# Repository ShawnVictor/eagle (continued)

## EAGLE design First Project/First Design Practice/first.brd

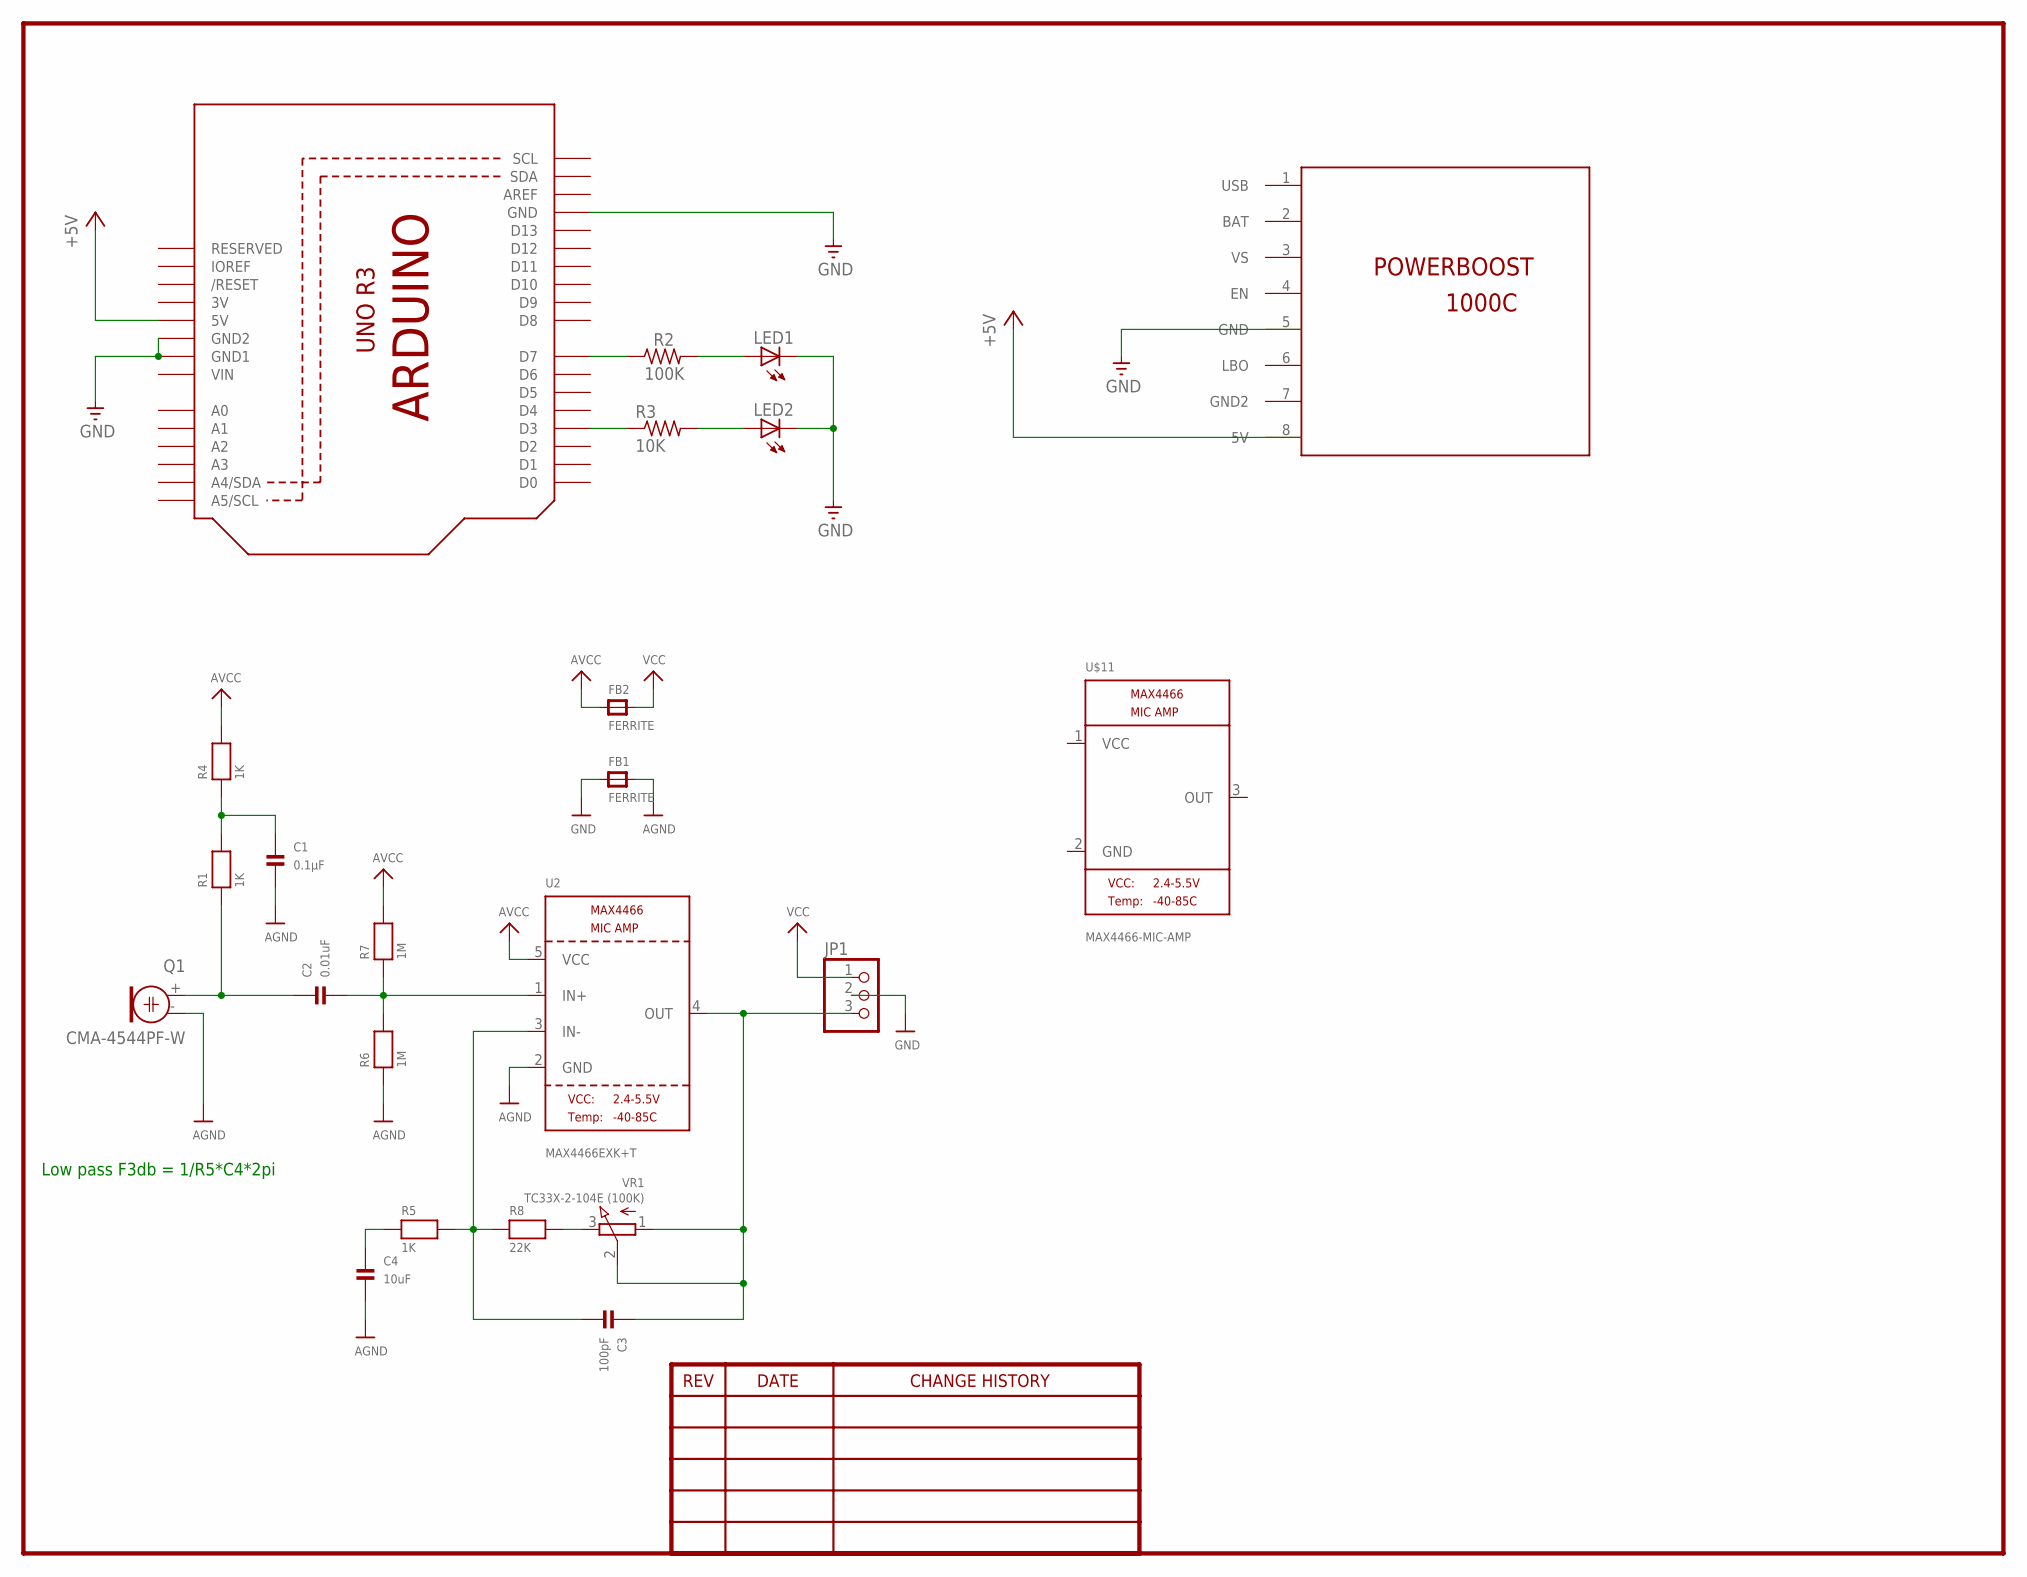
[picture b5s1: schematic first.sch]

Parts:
C1: 0.1µF; 0805
C2: 0.01uF; 0805
C3: 100pF; 0805
C4: 10uF; 0805
FB1, FB2: FERRITE; 0805
JP1: HEADER-1X376MIL; 1X03_ROUND_76
LED1, LED2: LED5MM
Q1: CMA-4544PF-W; ELECTRET_9.7
R1, R4, R5: 1K; 0805
R2: 100K; 0309/10
R3: 10K; 0309/10
R6, R7: 1M; 0805
R8: 22K; 0805
U1: ARDUINOR3-BPLACE
U2: MAX4466EXK+T; SC70-5
U$1: ADAFRUIT-POWERBOOST-1000C
U$11: MAX4466-MIC-AMP; MAX4466
VR1: TC33X-2-104E (100K); TRIMPOT_BOURNS_TC33X-2

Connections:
3V: U1.3V
+5V: U1.5V, U$1.8 (5V)
AGND: C1.2, C4.2, FB1.2, Q1.- (1), R6.1, U2.2 (GND)
AVCC: FB2.1, R4.2, R7.2, U2.5 (VCC)
GND: FB1.1, JP1.2, LED1.K (C), LED2.K (C), U1.GND, U1.GND1, U1.GND2, U$1.5 (GND)
unnamed: R2.1, U1.D7
unnamed: R3.1, U1.D3
unnamed: LED1.A, R2.2
unnamed: C2.1, Q1.+ (2), R1.1
unnamed: LED2.A, R3.2
unnamed: C1.1, R1.2, R4.1
unnamed: C2.2, R6.2, R7.1, U2.1 (IN+)
unnamed: C3.1, JP1.3, U2.4 (OUT), VR1.1 (A), VR1.2 (S)
unnamed: C3.2, R5.2, R8.1, U2.3 (IN-)
unnamed: C4.1, R5.1
unnamed: R8.2, VR1.3 (E)
VCC: FB2.2, JP1.1
VIN: U1.VIN

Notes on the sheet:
Low pass F3db = 1/R5*C4*2pi

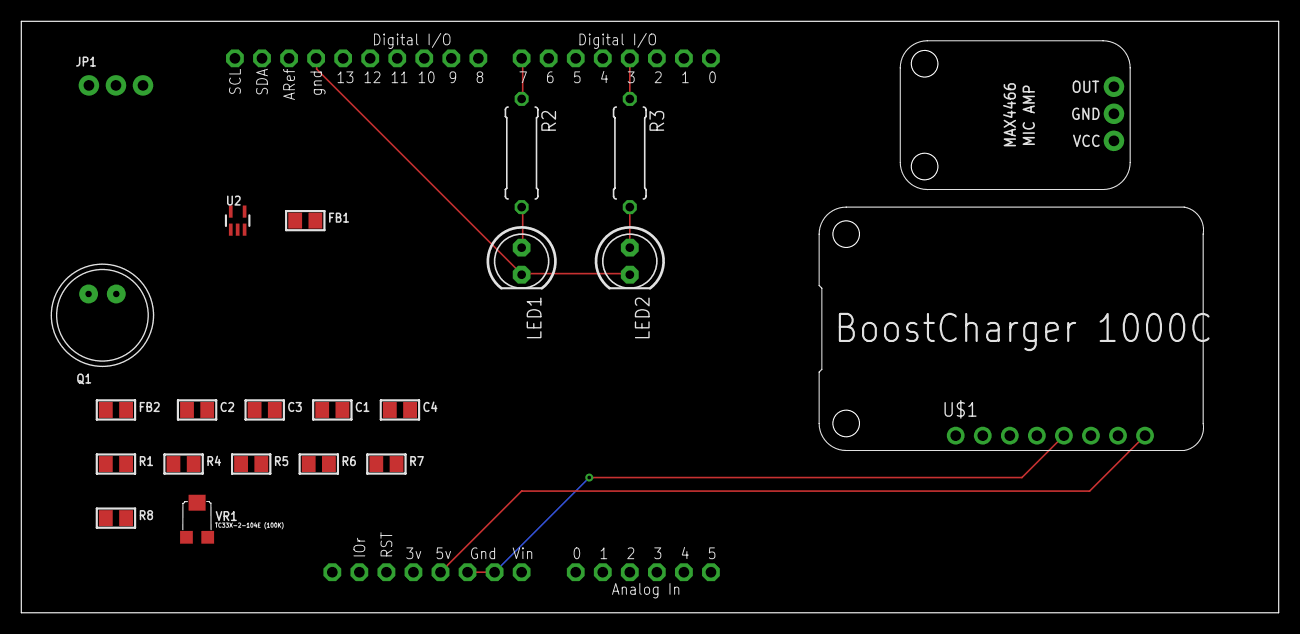
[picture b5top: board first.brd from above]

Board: 2 copper layers, 118.1 x 55.5 mm, 23 parts (0 on the bottom side), 16 nets.

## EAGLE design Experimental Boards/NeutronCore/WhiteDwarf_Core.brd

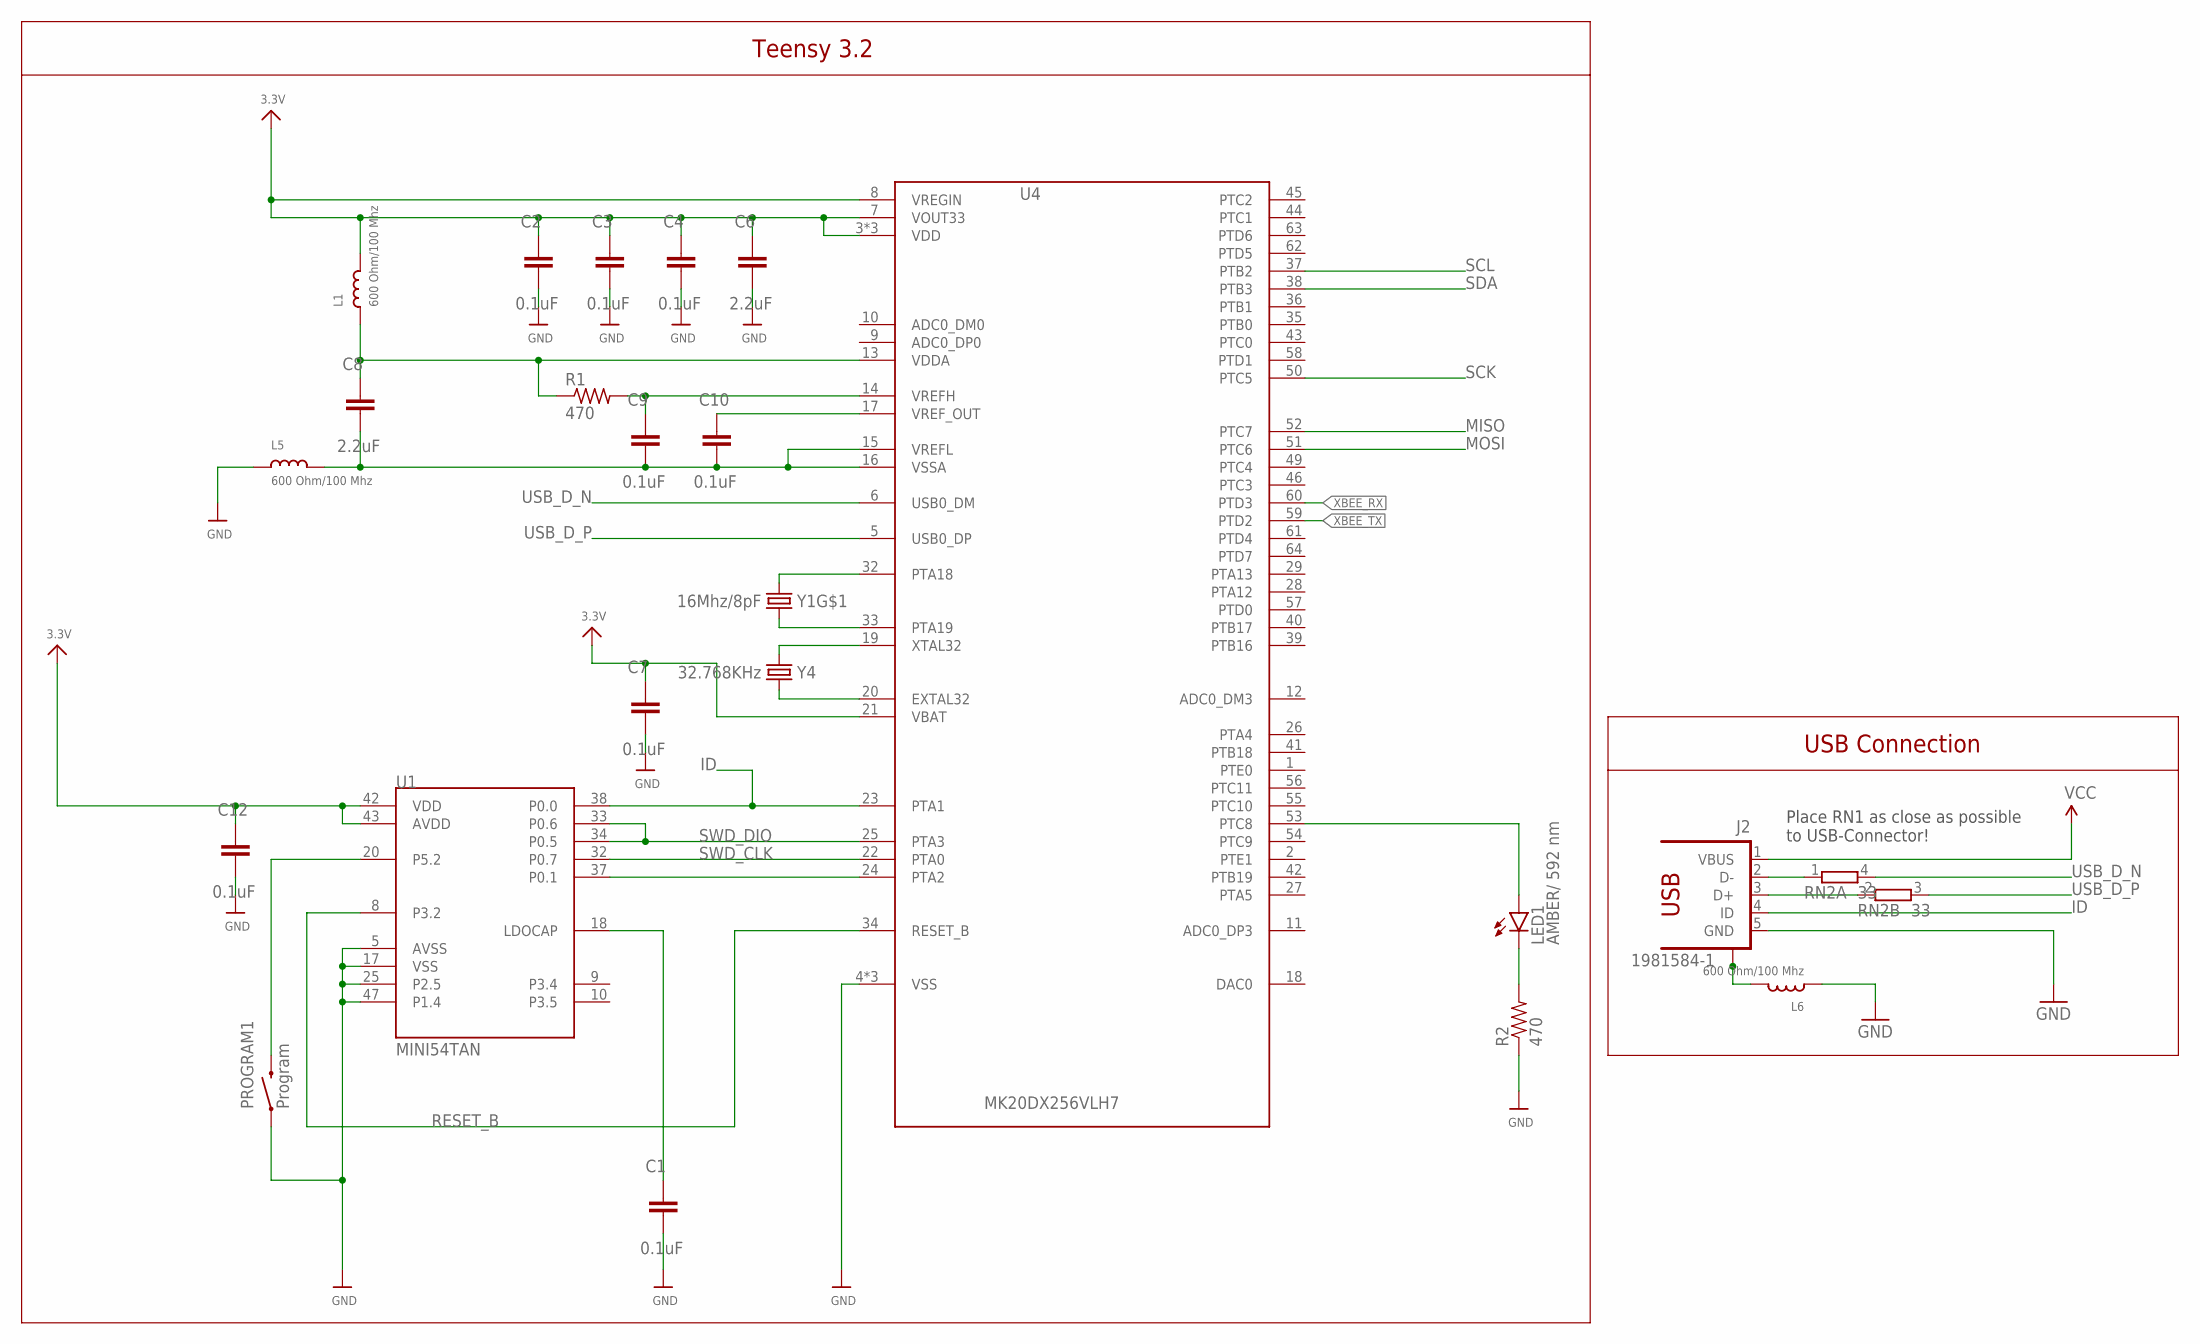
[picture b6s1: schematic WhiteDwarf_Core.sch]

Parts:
C1, C2, C3, C4, C7, C9, C10, C12: 0.1uF; CAP_0402
C6, C8: 2.2uF; CAP_0402
J2: 1981584-1; MPN ZX62-AB-5PA(11)
L1, L5, L6: 600 Ohm/100 Mhz; 0805
LED1: AMBER/ 592 nm; LED-0603
PROGRAM1: Program; TACTILE-SWITCH-1101NE; MPN RS-282G05A3-SM RT
R1: 470; RES_0402
R2: 470; 0603-RES
RN2: 33; EXB34V; MPN EXB-34V330JV
U1: MINI54TAN
U4: MK20DX256VLH7; MPN MK20DX256VLH7
Y1: 16Mhz/8pF; CRYSTAL-SMD-5X3; MPN ECS-160-8-30B-CKM
Y4: 32.768KHz; CRYSTAL-TXC-7A; MPN FC-255 32.7680K-A3

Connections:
3.3V: C2.1, C3.1, C4.1, C6.1, C7.1, C12.1, L1.2, U1.42 (VDD), U1.43 (AVDD), U4.3 (VDD), U4.7 (VOUT33), U4.8 (VREGIN), U4.21 (VBAT), U4.30 (VDD), U4.48 (VDD)
GND: C1.2, C2.2, C3.2, C4.2, C6.2, C7.2, C12.2, J2.5 (GND), L5.1, L6.1, PROGRAM1.P$1 (1), R2.1, U1.5 (AVSS), U1.17 (VSS), U1.25 (P2.5), U1.47 (P1.4), U4.4 (VSS), U4.31 (VSS), U4.47 (VSS)
ID: J2.4 (ID), U1.38 (P0.0), U4.23 (PTA1)
MISO: U4.52 (PTC7)
MOSI: U4.51 (PTC6)
unnamed: U1.37 (P0.1), U4.24 (PTA2)
unnamed: PROGRAM1.P$2 (2), U1.20 (P5.2)
unnamed: C1.1, U1.18 (LDOCAP)
unnamed: U4.32 (PTA18), Y1.3 (2)
unnamed: U4.33 (PTA19), Y1.1
unnamed: U4.19 (XTAL32), Y4.P$2 (2)
unnamed: U4.20 (EXTAL32), Y4.P$1 (1)
unnamed: LED1.A, U4.53 (PTC8)
unnamed: LED1.C, R2.2
RESET_B: U1.8 (P3.2), U4.34 (RESET_B)
SCK: U4.50 (PTC5)
SCL: U4.37 (PTB2)
SDA: U4.38 (PTB3)
SWD_CLK: U1.32 (P0.7), U4.22 (PTA0)
SWD_DIO: U1.33 (P0.6), U1.34 (P0.5), U4.25 (PTA3)
USB_CON_N1: J2.2 (D-), RN2.1
USB_CON_P1: J2.3 (D+), RN2.2 (1)
USB_D_N: RN2.4 (2), U4.6 (USB0_DM)
USB_D_P: RN2.3 (2), U4.5 (USB0_DP)
USB_SHIELD1: J2.S1, J2.S2, J2.S3, J2.S4, L6.2
VCC: J2.1 (VBUS)
VDDA1: C8.1, L1.1, R1.1, U4.13 (VDDA)
VREFH1: C9.1, R1.2, U4.14 (VREFH)
VREFL1: C8.2, C9.2, C10.2, L5.2, U4.15 (VREFL), U4.16 (VSSA)
VREF_OUT1: C10.1, U4.17 (VREF_OUT)
XBEE_RX: U4.60 (PTD3)
XBEE_TX: U4.59 (PTD2)

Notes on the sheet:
Teensy 3.2
Place RN1 as close as possible to USB-Connector!
USB Connection

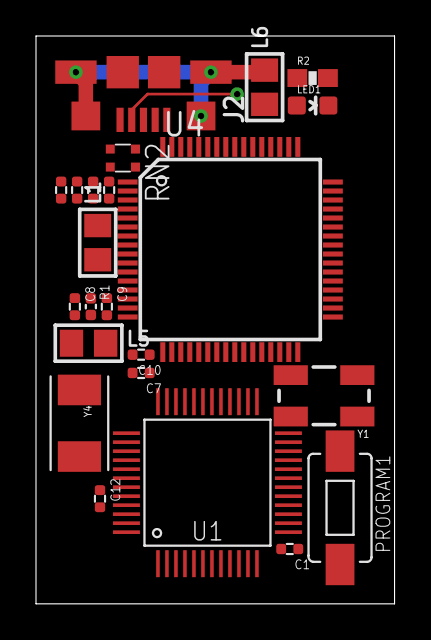
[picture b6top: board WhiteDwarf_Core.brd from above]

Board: 2 copper layers, 19.9 x 31.5 mm, 23 parts (0 on the bottom side), 24 nets.

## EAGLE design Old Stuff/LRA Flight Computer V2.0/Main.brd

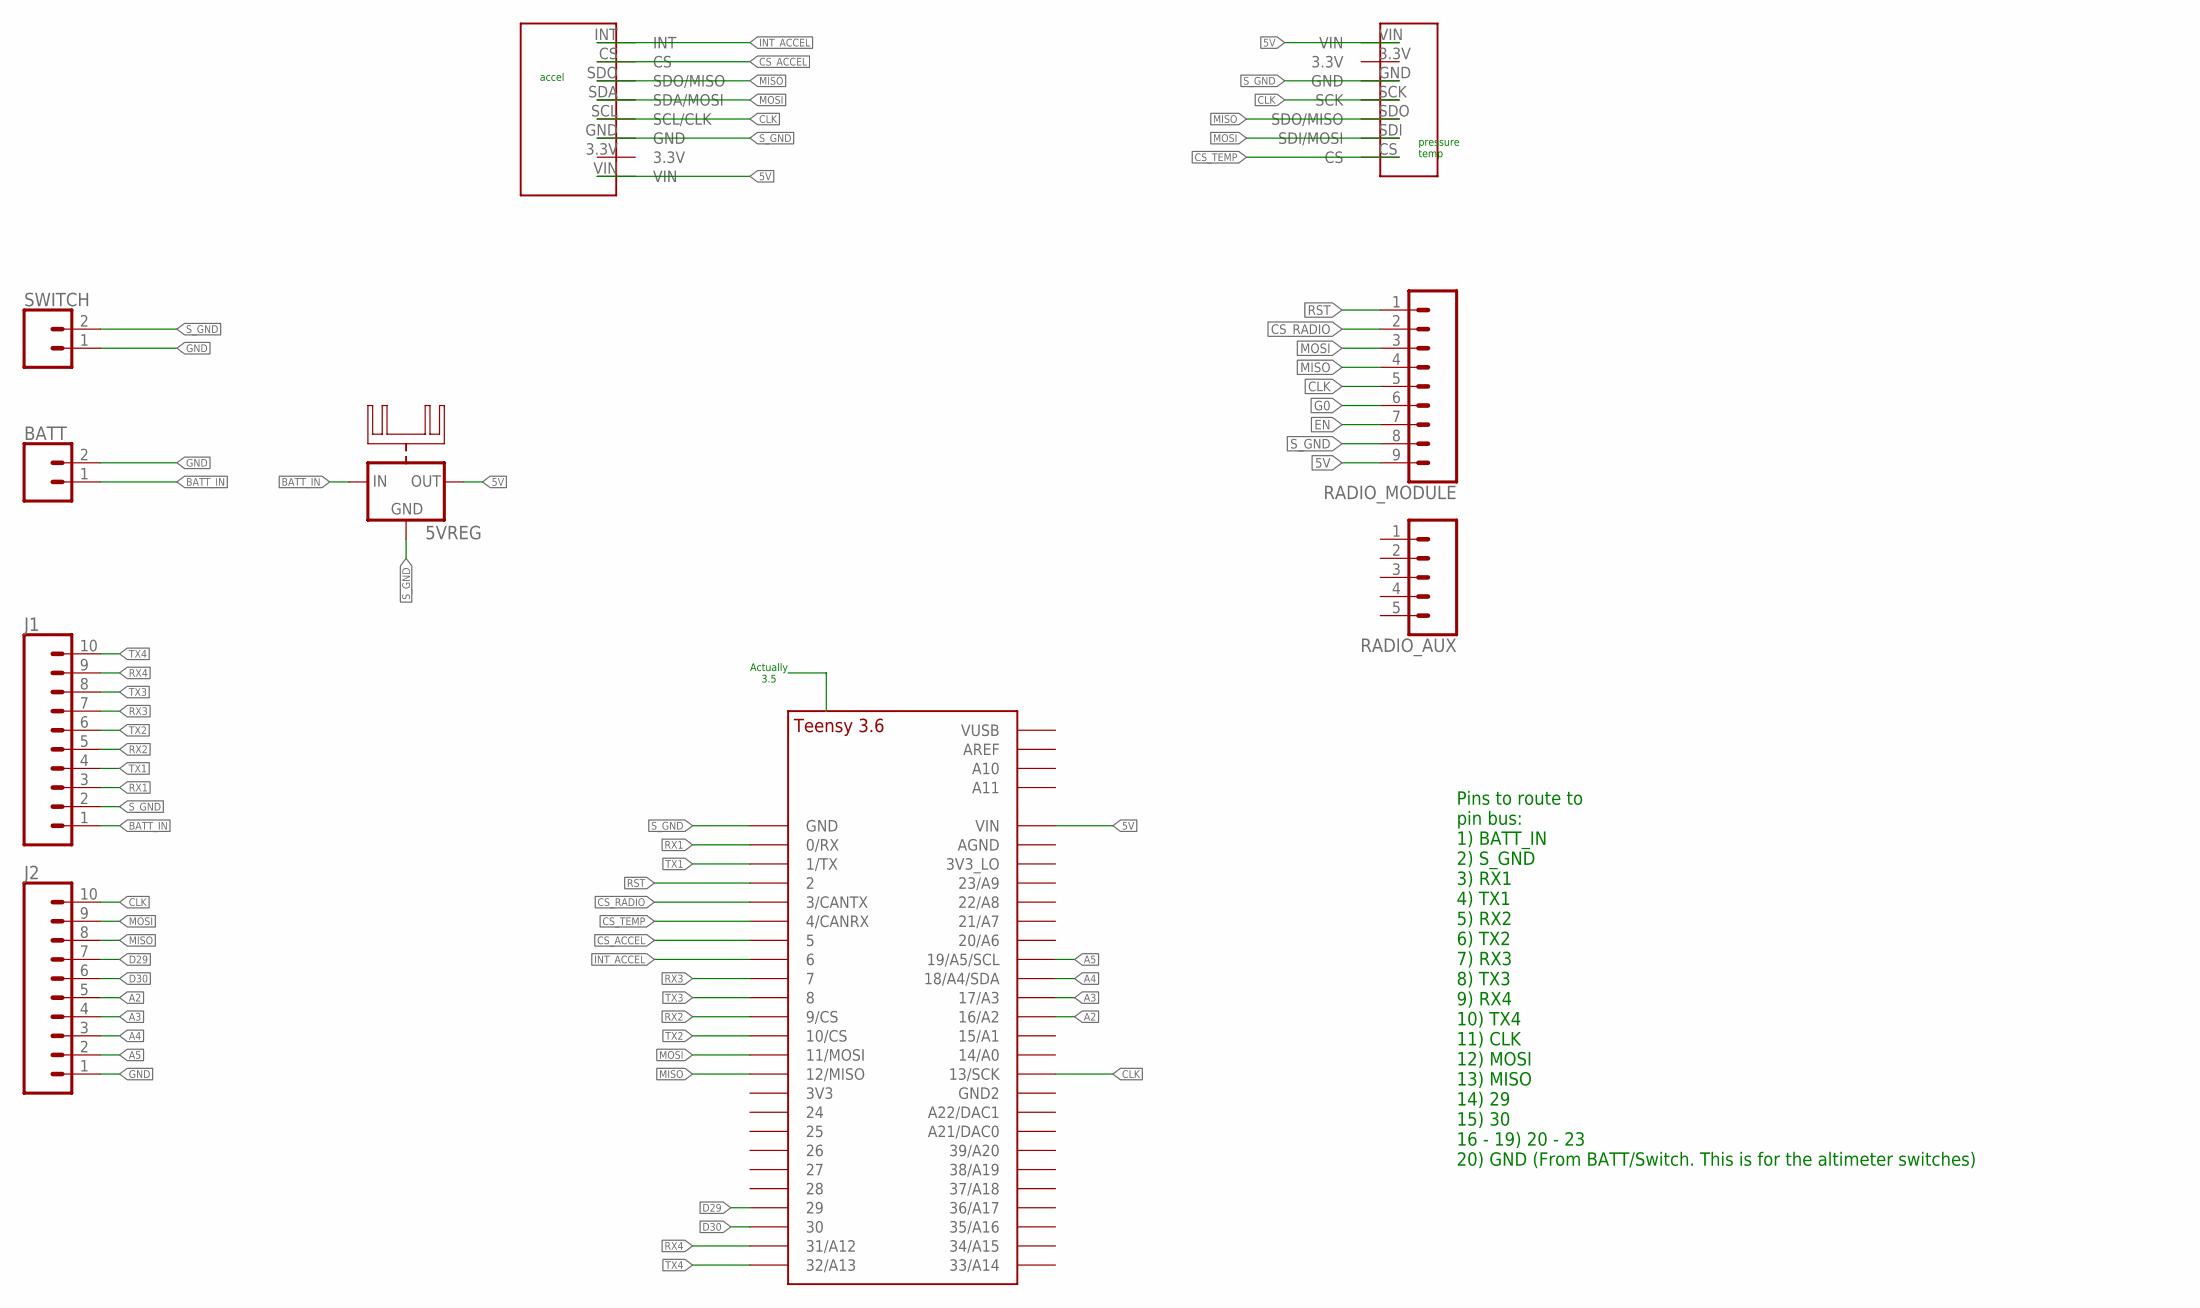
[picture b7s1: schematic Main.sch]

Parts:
5VREG: 78XXH
BATT: CONN_02-JST-2-PTH-NO_SILK; JST-2-PTH-NS
J1, J2: CONN_10"; 1X10
RADIO_AUX: CONN_05; 1X05
RADIO_MODULE: CONN_09; 1X09
SWITCH: CONN_02-JST-2-PTH-NO_SILK; JST-2-PTH-NS
U$1: TEENSY_3.5/3.6_BASIC
U$2: LIS3DH
U$3: BMP280

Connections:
5V: 5VREG.OUT, RADIO_MODULE.9, U$1.VIN, U$2.VIN, U$3.VIN
A2: J2.5, U$1.16/A2
A3: J2.4, U$1.17/A3
A4: J2.3, U$1.18/A4/SDA
A5: J2.2, U$1.19/A5/SCL
BATT_IN: 5VREG.IN, BATT.1, J1.1
CLK: J2.10, RADIO_MODULE.5, U$1.13/SCK, U$2.SCL (SCL/CLK), U$3.SCK
CS_ACCEL: U$1.5, U$2.CS
CS_RADIO: RADIO_MODULE.2, U$1.3/CANTX
CS_TEMP: U$1.4/CANRX, U$3.CS
D29: J2.7, U$1.29
D30: J2.6, U$1.30
EN: RADIO_MODULE.7
G0: RADIO_MODULE.6
GND: BATT.2, J2.1, SWITCH.1
INT_ACCEL: U$1.6, U$2.INT
MISO: J2.8, RADIO_MODULE.4, U$1.12/MISO, U$2.SDO (SDO/MISO), U$3.SDO (SDO/MISO)
MOSI: J2.9, RADIO_MODULE.3, U$1.11/MOSI, U$2.SDA (SDA/MOSI), U$3.SDI (SDI/MOSI)
RST: RADIO_MODULE.1, U$1.2
RX1: J1.3, U$1.0/RX
RX2: J1.5, U$1.9/CS
RX3: J1.7, U$1.7
RX4: J1.9, U$1.31/A12
S_GND: 5VREG.GND, J1.2, RADIO_MODULE.8, SWITCH.2, U$1.GND, U$2.GND, U$3.GND
TX1: J1.4, U$1.1/TX
TX2: J1.6, U$1.10/CS
TX3: J1.8, U$1.8
TX4: J1.10, U$1.32/A13

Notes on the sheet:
accel
pressure temp
Actually 3.5
Pins to route to pin bus: 1) BATT_IN 2) S_GND 3) RX1 4) TX1 5) RX2 6) TX2 7) RX3 8) TX3 9) RX4 10) TX4 11) CLK 12) MOSI 13) MISO 14) 29 15) 30 16 - 19) 20 - 23 20) GND (From BATT/Switch. This is for the altimeter switches)

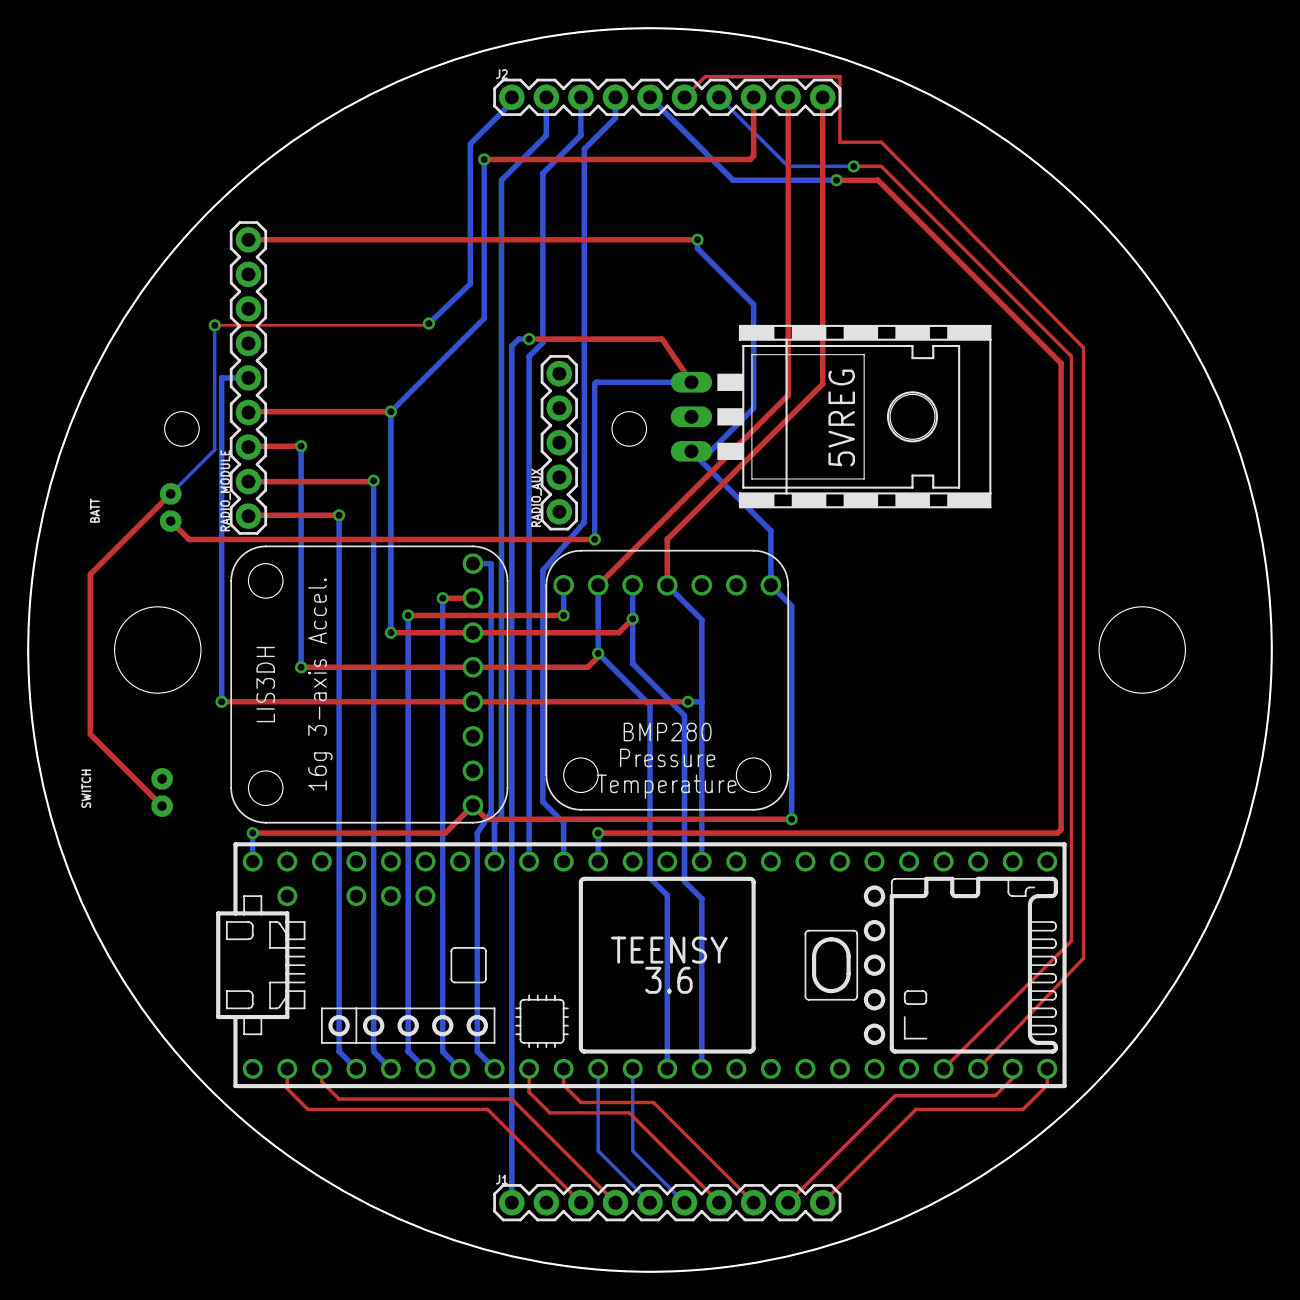
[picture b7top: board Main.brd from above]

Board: 2 copper layers, 91.4 x 91.4 mm, 10 parts (0 on the bottom side), 26 nets.

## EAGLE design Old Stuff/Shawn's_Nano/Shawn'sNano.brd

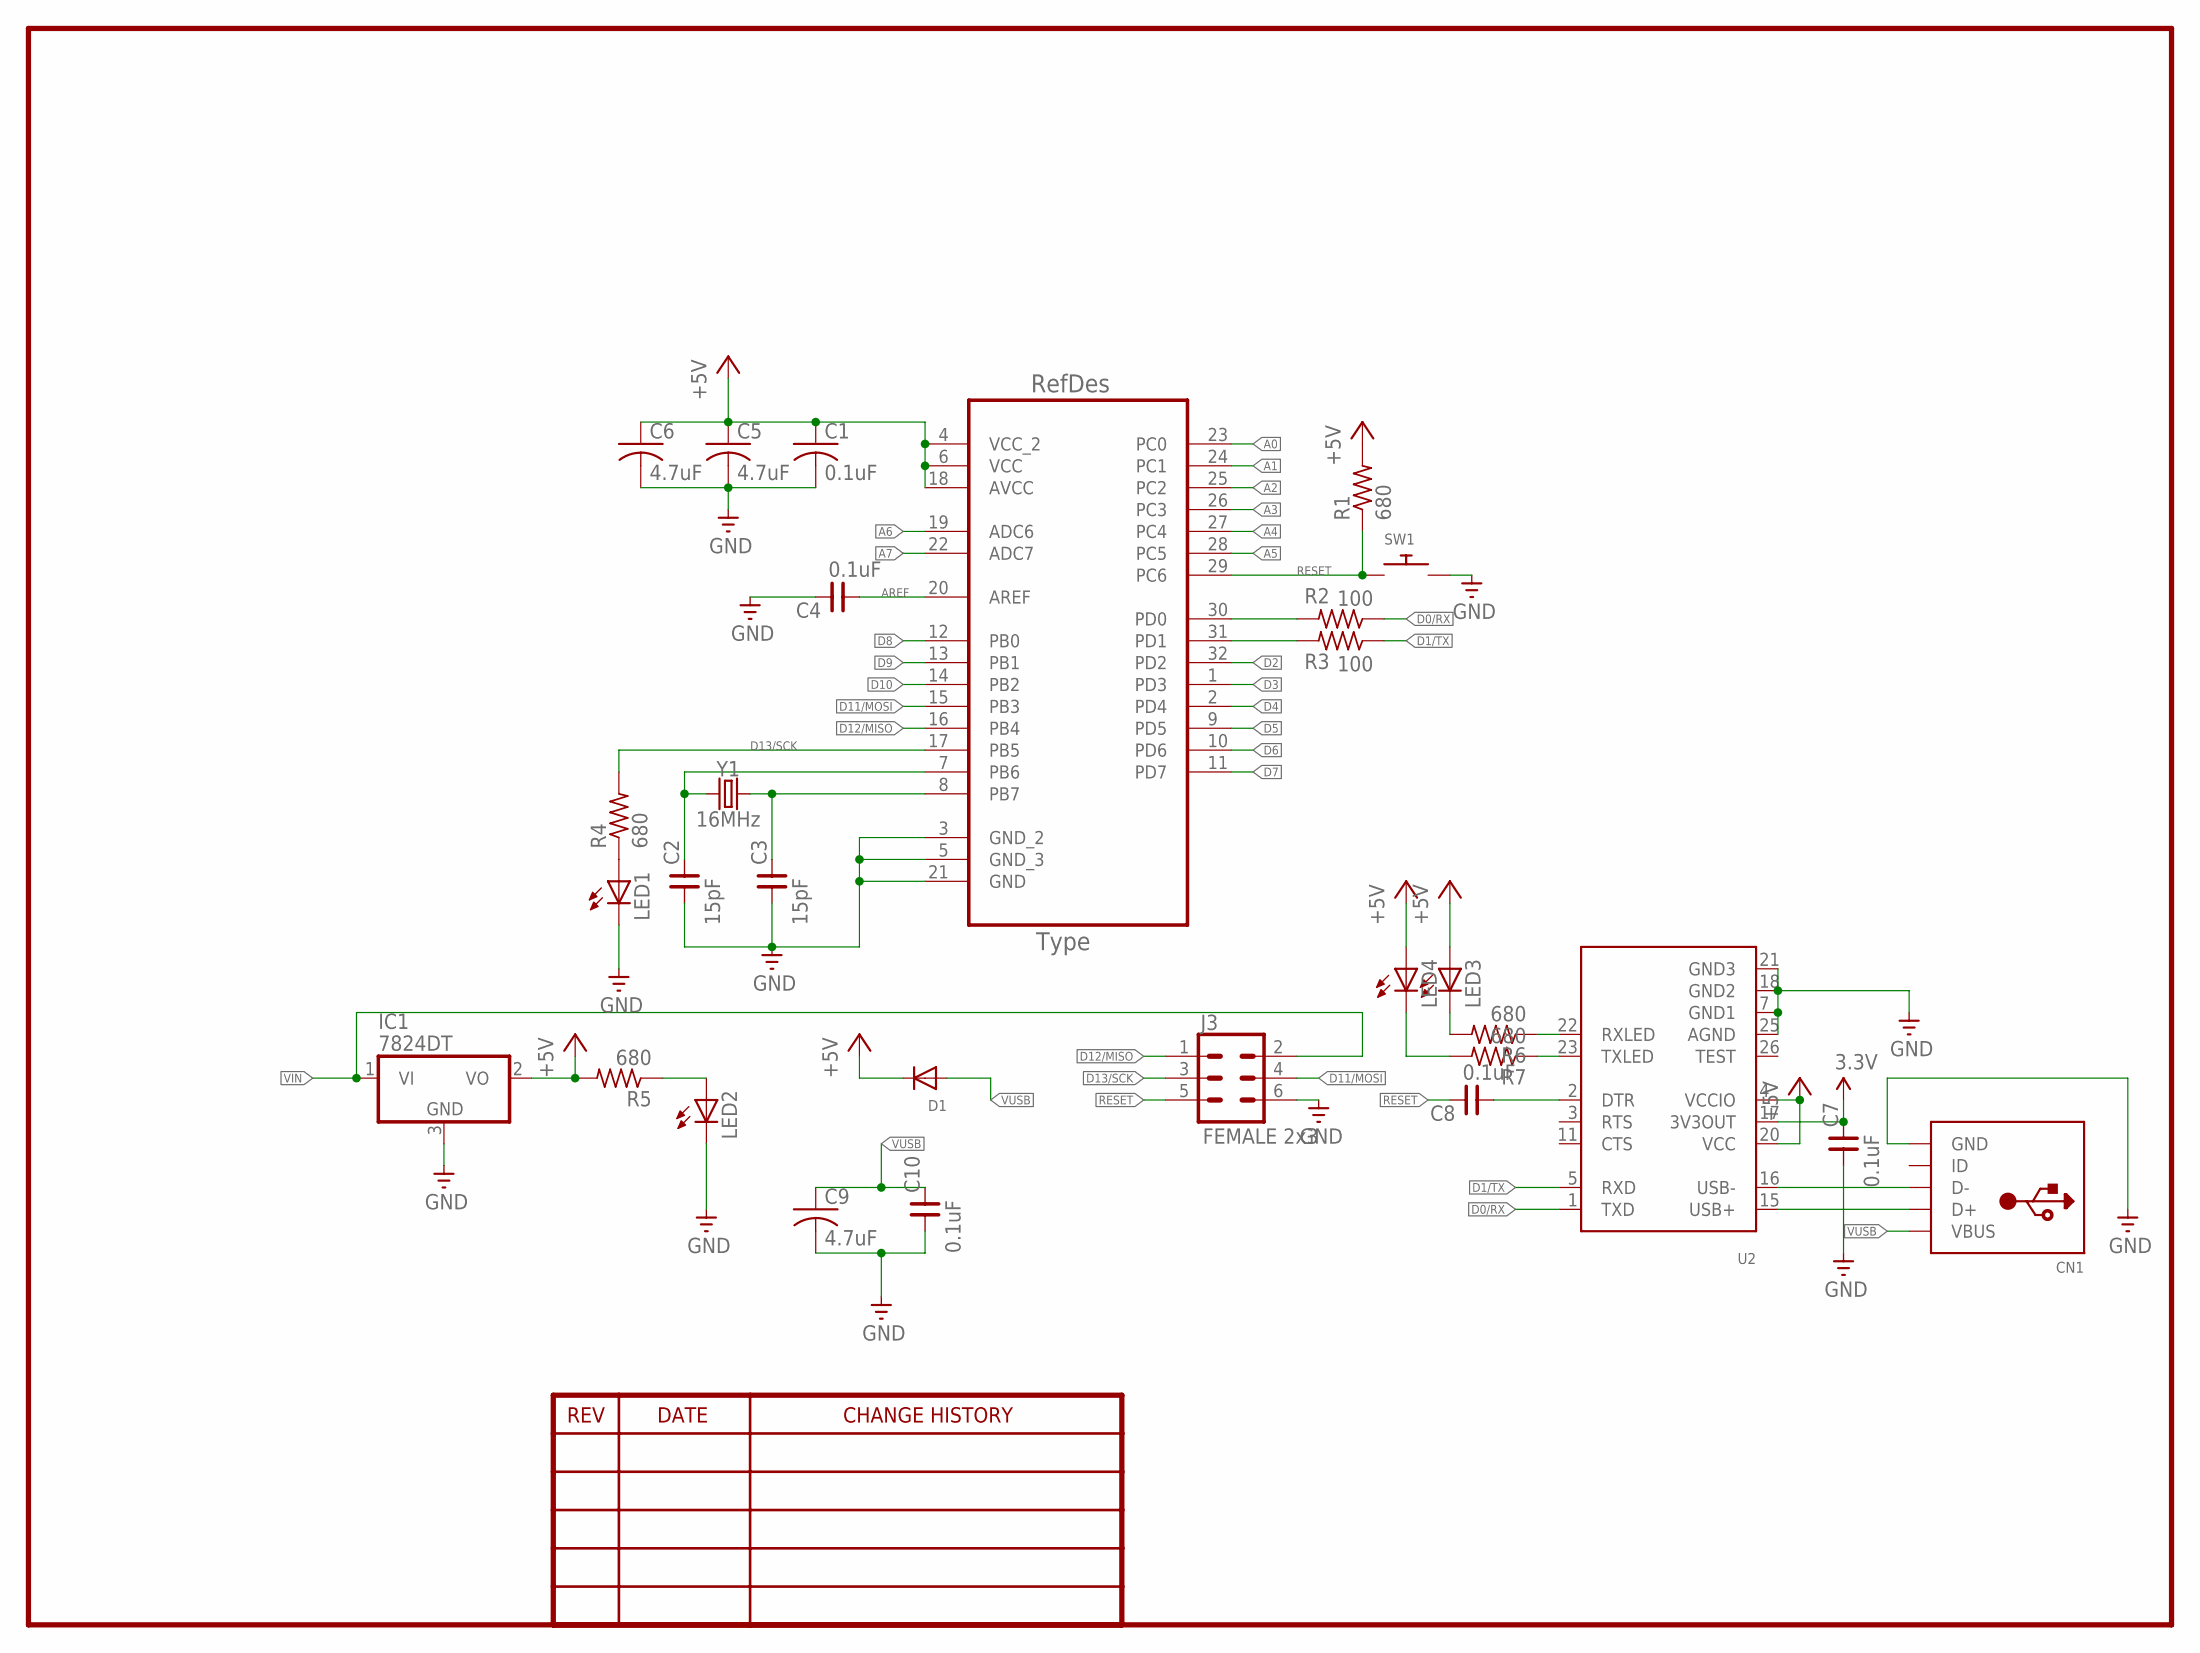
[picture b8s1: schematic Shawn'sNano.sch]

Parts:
C1: 0.1uF; C0805
C2, C3: 15pF; 0805
C4, C7, C8, C10: 0.1uF; 0805
C5, C6, C9: 4.7uF; C0805
CN1: USBMINIB; USB-MINIB
D1: DIODESOD-123; SOD-123
IC1: 7824DT; TO252
J3: FEMALE 2x3; 2X3
LED1, LED2, LED3, LED4: LEDCHIPLED_0805; CHIPLED_0805
R1, R4, R5, R6, R7: 680; R0805
R2, R3: 100; R0805
SW1: SWITCH_PUSHBUTTONEVQ-PE; TACT_PANA-EVQ
U1: ATMEGA328P-AU; QFP80P900X900X120-32N
U2: FT232RLSSOP28; SSOP28DB
Y1: 16MHz; HC49US

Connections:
3.3V: C7.2, U2.17 (3V3OUT)
+5V: C1.1, C5.1, C6.1, D1.C, IC1.2 (VO), LED3.A, LED4.A, R1.2, R5.2, U1.4 (VCC_2), U1.6 (VCC), U1.18 (AVCC), U2.4 (VCCIO), U2.20 (VCC)
A0: U1.23 (PC0)
A1: U1.24 (PC1)
A2: U1.25 (PC2)
A3: U1.26 (PC3)
A4: U1.27 (PC4)
A5: U1.28 (PC5)
A6: U1.19 (ADC6)
A7: U1.22 (ADC7)
AREF: C4.1, U1.20 (AREF)
D0/RX: R2.1, U2.1 (TXD)
D1/TX: R3.1, U2.5 (RXD)
D2: U1.32 (PD2)
D3: U1.1 (PD3)
D4: U1.2 (PD4)
D5: U1.9 (PD5)
D6: U1.10 (PD6)
D7: U1.11 (PD7)
D8: U1.12 (PB0)
D9: U1.13 (PB1)
D10: U1.14 (PB2)
D11/MOSI: J3.4, U1.15 (PB3)
D12/MISO: J3.1, U1.16 (PB4)
D13/SCK: J3.3, R4.2, U1.17 (PB5)
GND: C1.2, C2.1, C3.1, C4.2, C5.2, C6.2, C7.1, C9.2, C10.1, CN1.GND, IC1.3 (GND), J3.6, LED1.C, LED2.C, SW1.P$2, U1.3 (GND_2), U1.5 (GND_3), U1.21 (GND), U2.7 (GND1), U2.18 (GND2), U2.21 (GND3), U2.25 (AGND)
unnamed: C3.2, U1.8 (PB7), Y1.2
unnamed: C2.2, U1.7 (PB6), Y1.1
unnamed: LED1.A, R4.1
unnamed: LED2.A, R5.1
unnamed: CN1.D+, U2.15 (USB+)
unnamed: CN1.D-, U2.16 (USB-)
unnamed: R2.2, U1.30 (PD0)
unnamed: R3.2, U1.31 (PD1)
unnamed: LED3.C, R6.2
unnamed: R6.1, U2.22 (RXLED)
unnamed: R7.1, U2.23 (TXLED)
unnamed: C8.1, U2.2 (DTR)
unnamed: LED4.C, R7.2
RESET: C8.2, J3.5, R1.1, SW1.P$1, U1.29 (PC6)
VIN: IC1.1 (VI), J3.2
VUSB: C9.1, C10.2, CN1.VBUS, D1.A

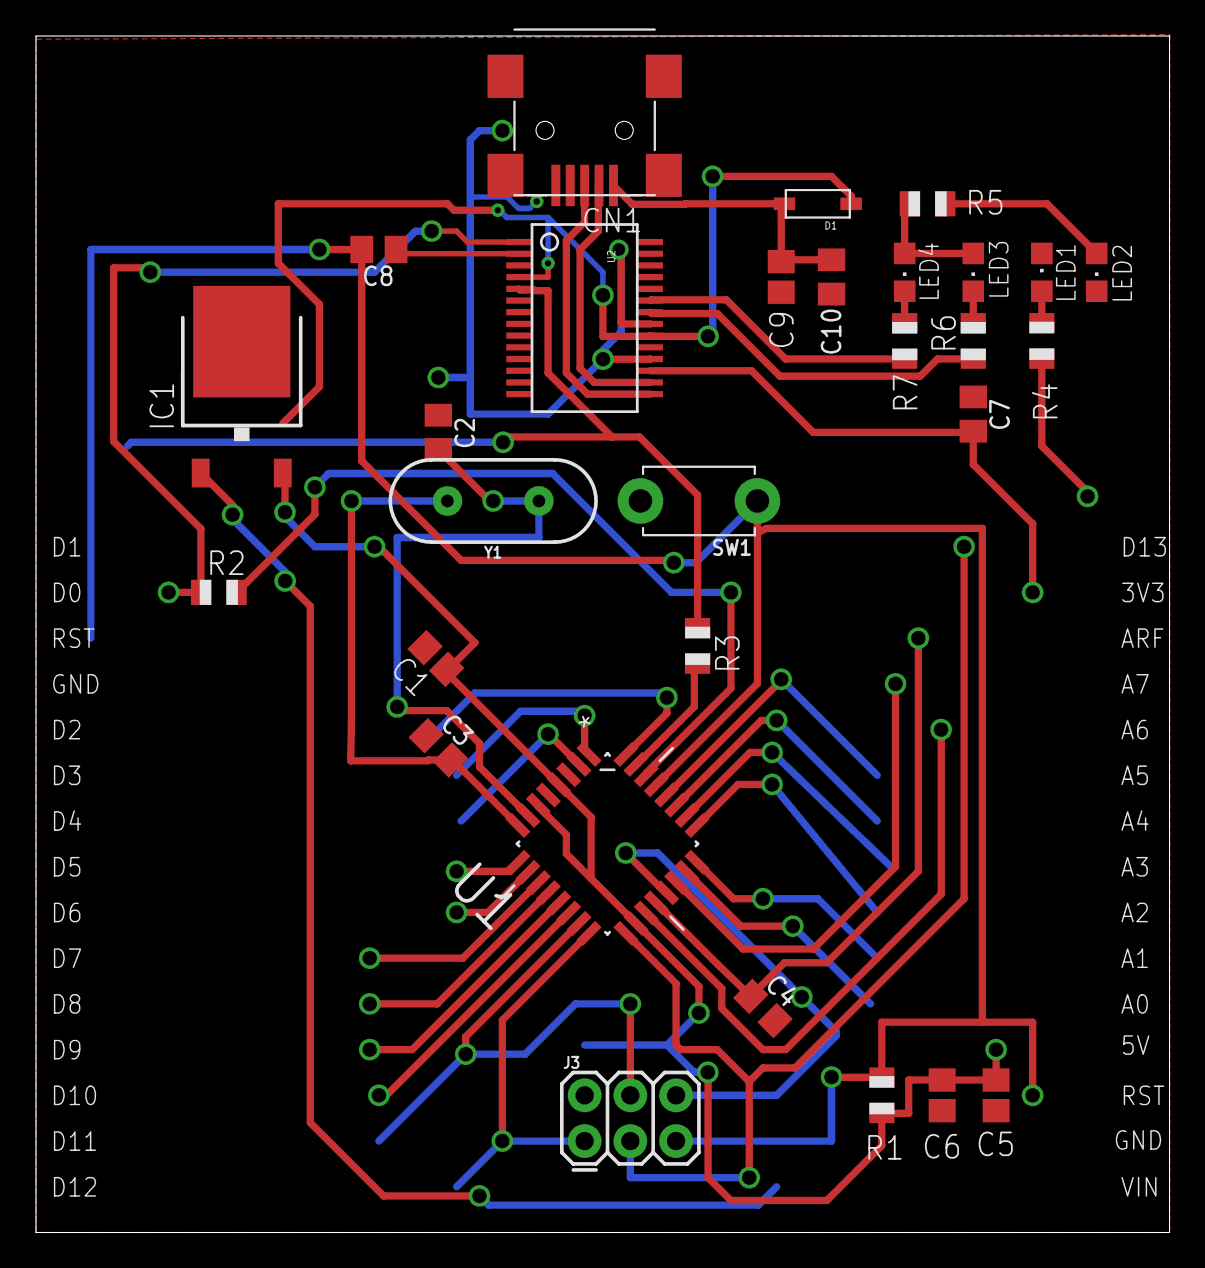
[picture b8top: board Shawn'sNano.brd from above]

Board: 2 copper layers, 63.0 x 66.5 mm, 29 parts (0 on the bottom side), 25 nets.

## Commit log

2020-04-23 All files from Shawn's Laptop
2020-04-24 Added Desktop Files
2020-05-12 Added Experimental Boards/ Gravity Board/ Home Automation Boards
2020-05-12 V0 Final Design
2020-05-12 V1 dev
2020-05-19 Added DC2DC Conv, EEPROM, Got rid of Coin Cell, Added Switch
2020-05-19 Add Communication Pins, Need to connect headers to signals.
2020-05-27 Moved Headers, SMA. Added LED.
2020-05-30 Moved Holes/LED around, modfied SPI Pins,began routing.
2020-05-30 Completed a large portion of routing
2020-05-30 Completed Routing and Fixed DRC Errors. Need to Perfrom Final Check w/ Butch and Selfcheck.
2020-06-04 Added CAN Resistor, GPS GND Line Connected, Fixed Decoup Cap Value for AUX 3V3, Fixed Switch to not extend board size
2020-06-12 Made final changes to brd and revised Gerber, awaiting status.
